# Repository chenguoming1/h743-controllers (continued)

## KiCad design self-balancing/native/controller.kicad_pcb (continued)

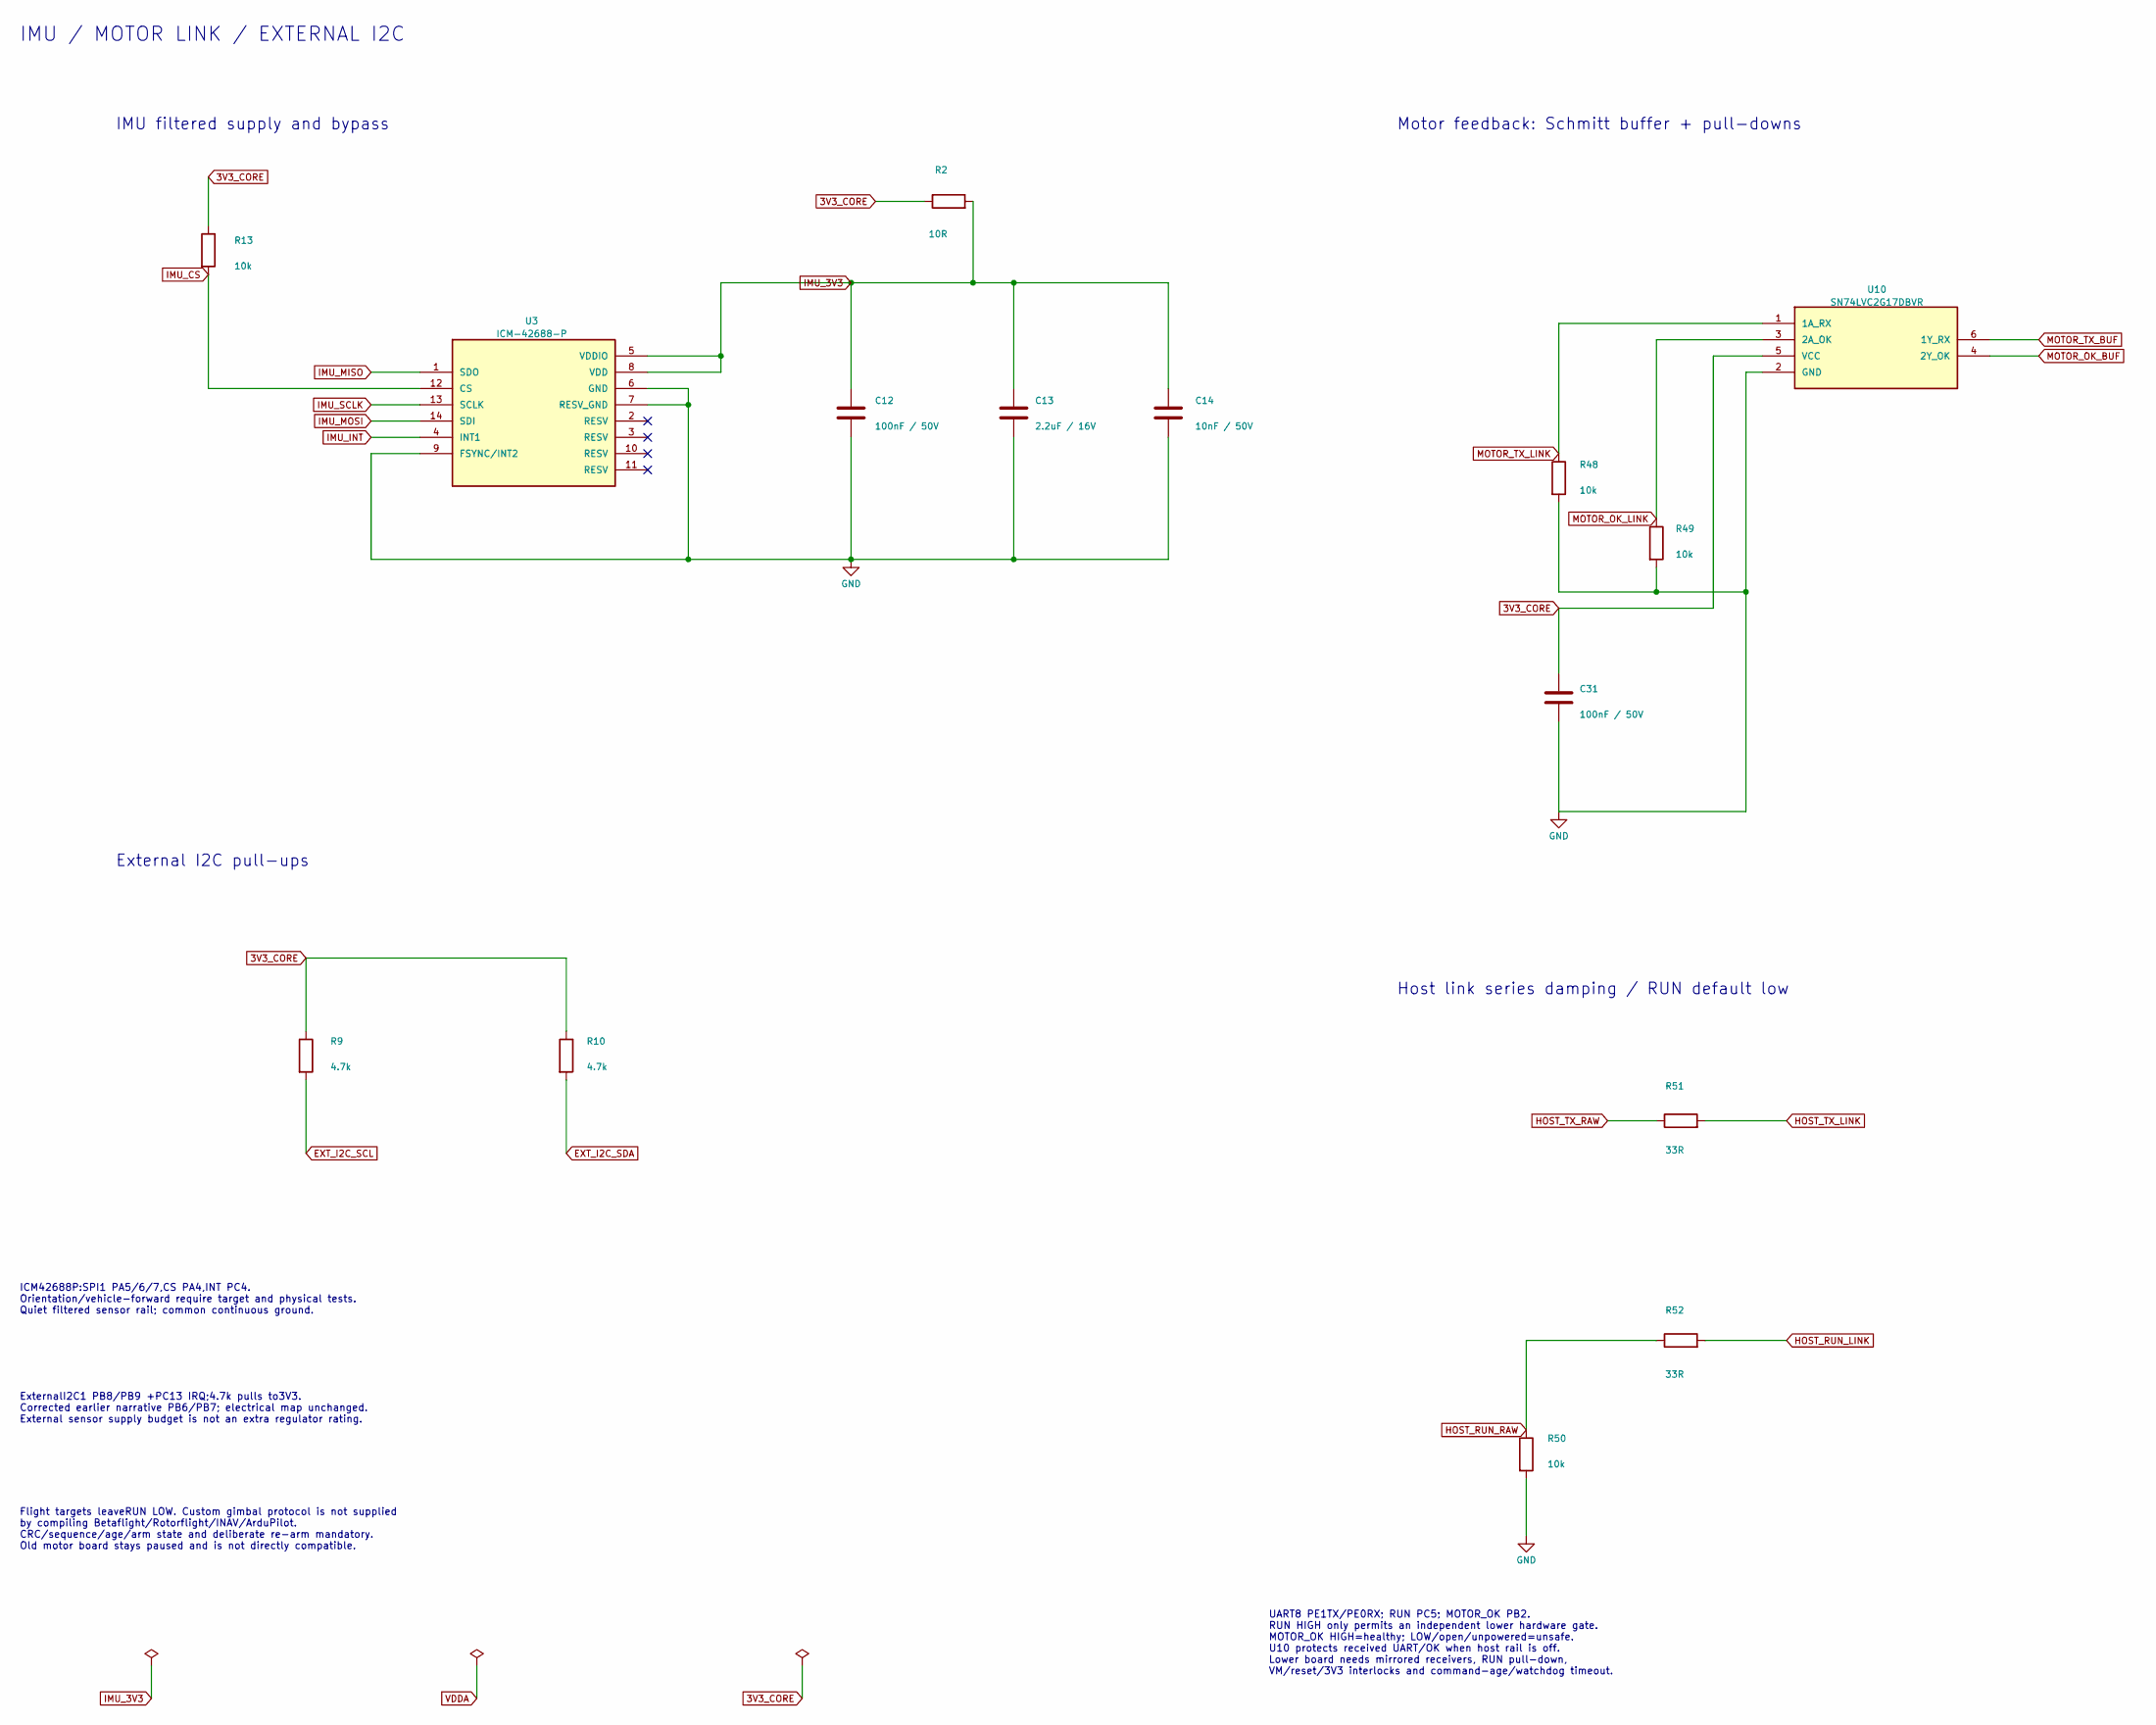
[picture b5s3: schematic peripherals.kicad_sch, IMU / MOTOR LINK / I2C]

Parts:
C12: 100nF / 50V; C12_C_0603_1608Metric; Manufacturer_Part_Number CC0603KRX7R9BB104; LCSC C14663
C13: 2.2uF / 16V; C13_C_0603_1608Metric; Manufacturer_Part_Number CL10A225KO8NNNC; LCSC C23630
C14: 10nF / 50V; C14_C_0603_1608Metric; Manufacturer_Part_Number 0603B103K500NT; LCSC C57112
C31: 100nF / 50V; C31_C_0603_1608Metric; Manufacturer_Part_Number CC0603KRX7R9BB104; LCSC C14663
R2: 10R; R2_R_0603_1608Metric; Manufacturer_Part_Number 0603WAF100JT5E; LCSC C22859
R9: 4.7k; R9_R_0603_1608Metric; Manufacturer_Part_Number 0603WAF4701T5E; LCSC C23162
R10: 4.7k; R10_R_0603_1608Metric; Manufacturer_Part_Number 0603WAF4701T5E; LCSC C23162
R13: 10k; R13_R_0603_1608Metric; Manufacturer_Part_Number 0603WAF1002T5E; LCSC C25804
R48: 10k; R48_R_0603_1608Metric; Manufacturer_Part_Number 0603WAF1002T5E; LCSC C25804
R49: 10k; R49_R_0603_1608Metric; Manufacturer_Part_Number 0603WAF1002T5E; LCSC C25804
R50: 10k; R50_R_0603_1608Metric; Manufacturer_Part_Number 0603WAF1002T5E; LCSC C25804
R51: 33R; R51_R_0603_1608Metric; Manufacturer_Part_Number 0603WAF330JT5E; LCSC C23140
R52: 33R; R52_R_0603_1608Metric; Manufacturer_Part_Number 0603WAF330JT5E; LCSC C23140
U3: ICM-42688-P; U3_LGA-14_3x2.5mm_P0.5mm_LayoutBorder3x4y; Manufacturer_Part_Number ICM-42688-P; LCSC C1850418
U10: SN74LVC2G17DBVR; U10_SOT-23-6; Manufacturer_Part_Number SN74LVC2G17DBVR; LCSC C10429

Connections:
EXT_I2C_SCL: R9.2; also elsewhere on the board
EXT_I2C_SDA: R10.2; also elsewhere on the board
GND: C12.2, C13.2, C14.2, C31.2, R48.2, R49.2, R50.2, U3.6 (GND), U3.7 (RESV_GND), U3.9 (FSYNC/INT2), U10.2 (GND); also elsewhere on the board
HOST_RUN_LINK: R52.2; also elsewhere on the board
HOST_RUN_RAW: R50.1, R52.1; also elsewhere on the board
HOST_TX_LINK: R51.2; also elsewhere on the board
HOST_TX_RAW: R51.1; also elsewhere on the board
IMU_3V3: C12.1, C13.1, C14.1, R2.2, U3.5 (VDDIO), U3.8 (VDD)
IMU_CS: R13.2, U3.12 (CS); also elsewhere on the board
IMU_INT: U3.4 (INT1); also elsewhere on the board
IMU_MISO: U3.1 (SDO); also elsewhere on the board
IMU_MOSI: U3.14 (SDI); also elsewhere on the board
IMU_SCLK: U3.13 (SCLK); also elsewhere on the board
MOTOR_OK_BUF: U10.4 (2Y_OK); also elsewhere on the board
MOTOR_OK_LINK: R49.1, U10.3 (2A_OK); also elsewhere on the board
MOTOR_TX_BUF: U10.6 (1Y_RX); also elsewhere on the board
MOTOR_TX_LINK: R48.1, U10.1 (1A_RX); also elsewhere on the board

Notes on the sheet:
IMU / MOTOR LINK / EXTERNAL I2C
IMU filtered supply and bypass
Motor feedback: Schmitt buffer + pull-downs
External I2C pull-ups
Host link series damping / RUN default low
ICM42688P:SPI1 PA5/6/7,CS PA4,INT PC4. Orientation/vehicle-forward require target and physical tests. Quiet filtered sensor rail; common continuous ground.
ExternalI2C1 PB8/PB9 +PC13 IRQ;4.7k pulls to3V3. Corrected earlier narrative PB6/PB7; electrical map unchanged. External sensor supply budget is not an extra regulator rating.
UART8 PE1TX/PE0RX; RUN PC5; MOTOR_OK PB2. RUN HIGH only permits an independent lower hardware gate. MOTOR_OK HIGH=healthy; LOW/open/unpowered=unsafe. U10 protects received UART/OK when host rail is off. Lower board needs mirrored receivers, RUN pull-down, VM/reset/3V3 interlocks and command-age/wat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
Flight targets leaveRUN LOW. Custom gimbal protocol is not supplied by compiling Betaflight/Rotorflight/INAV/ArduPilot. CRC/sequence/age/arm state and deliberate re-arm mandatory. Old motor board stays paused and is not directly compatible.

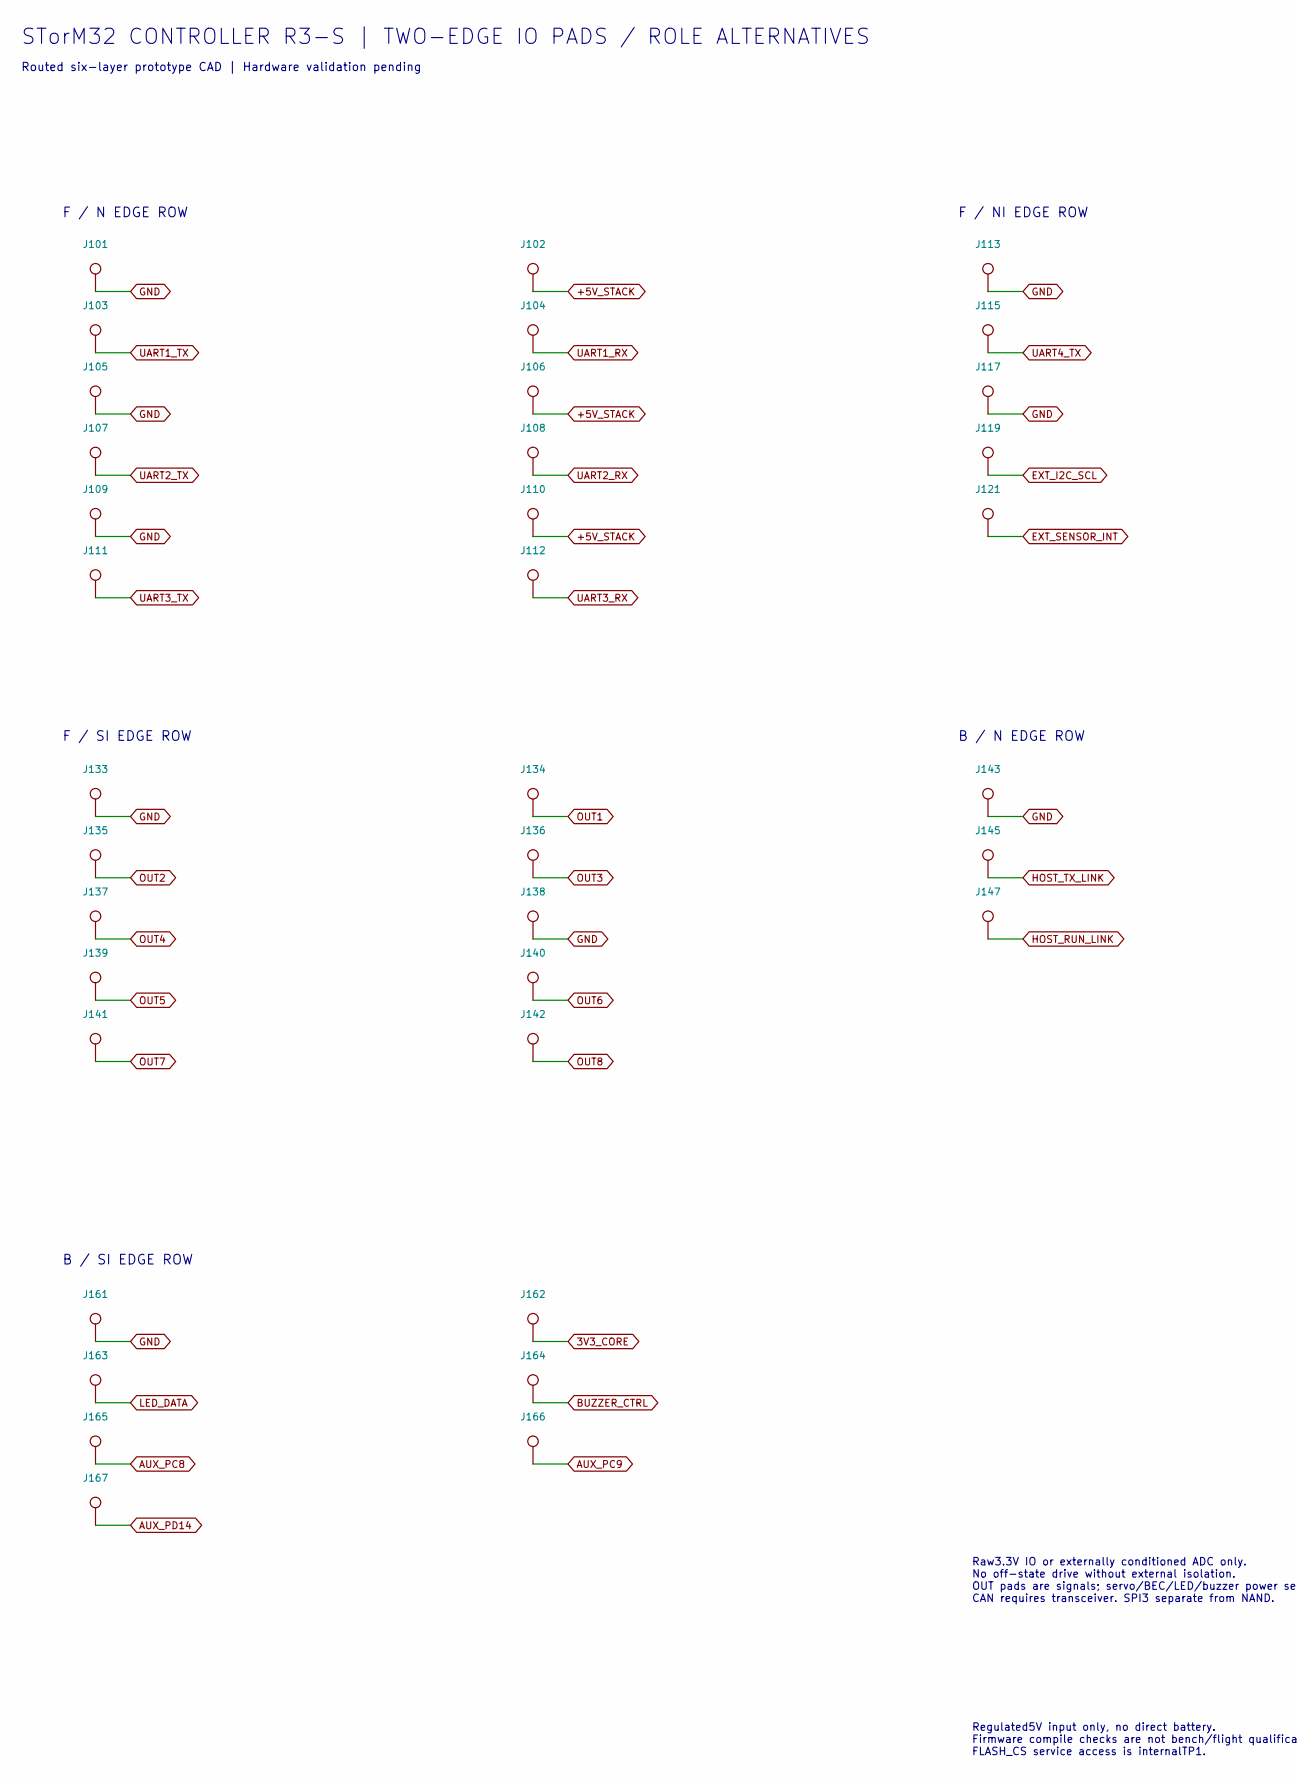
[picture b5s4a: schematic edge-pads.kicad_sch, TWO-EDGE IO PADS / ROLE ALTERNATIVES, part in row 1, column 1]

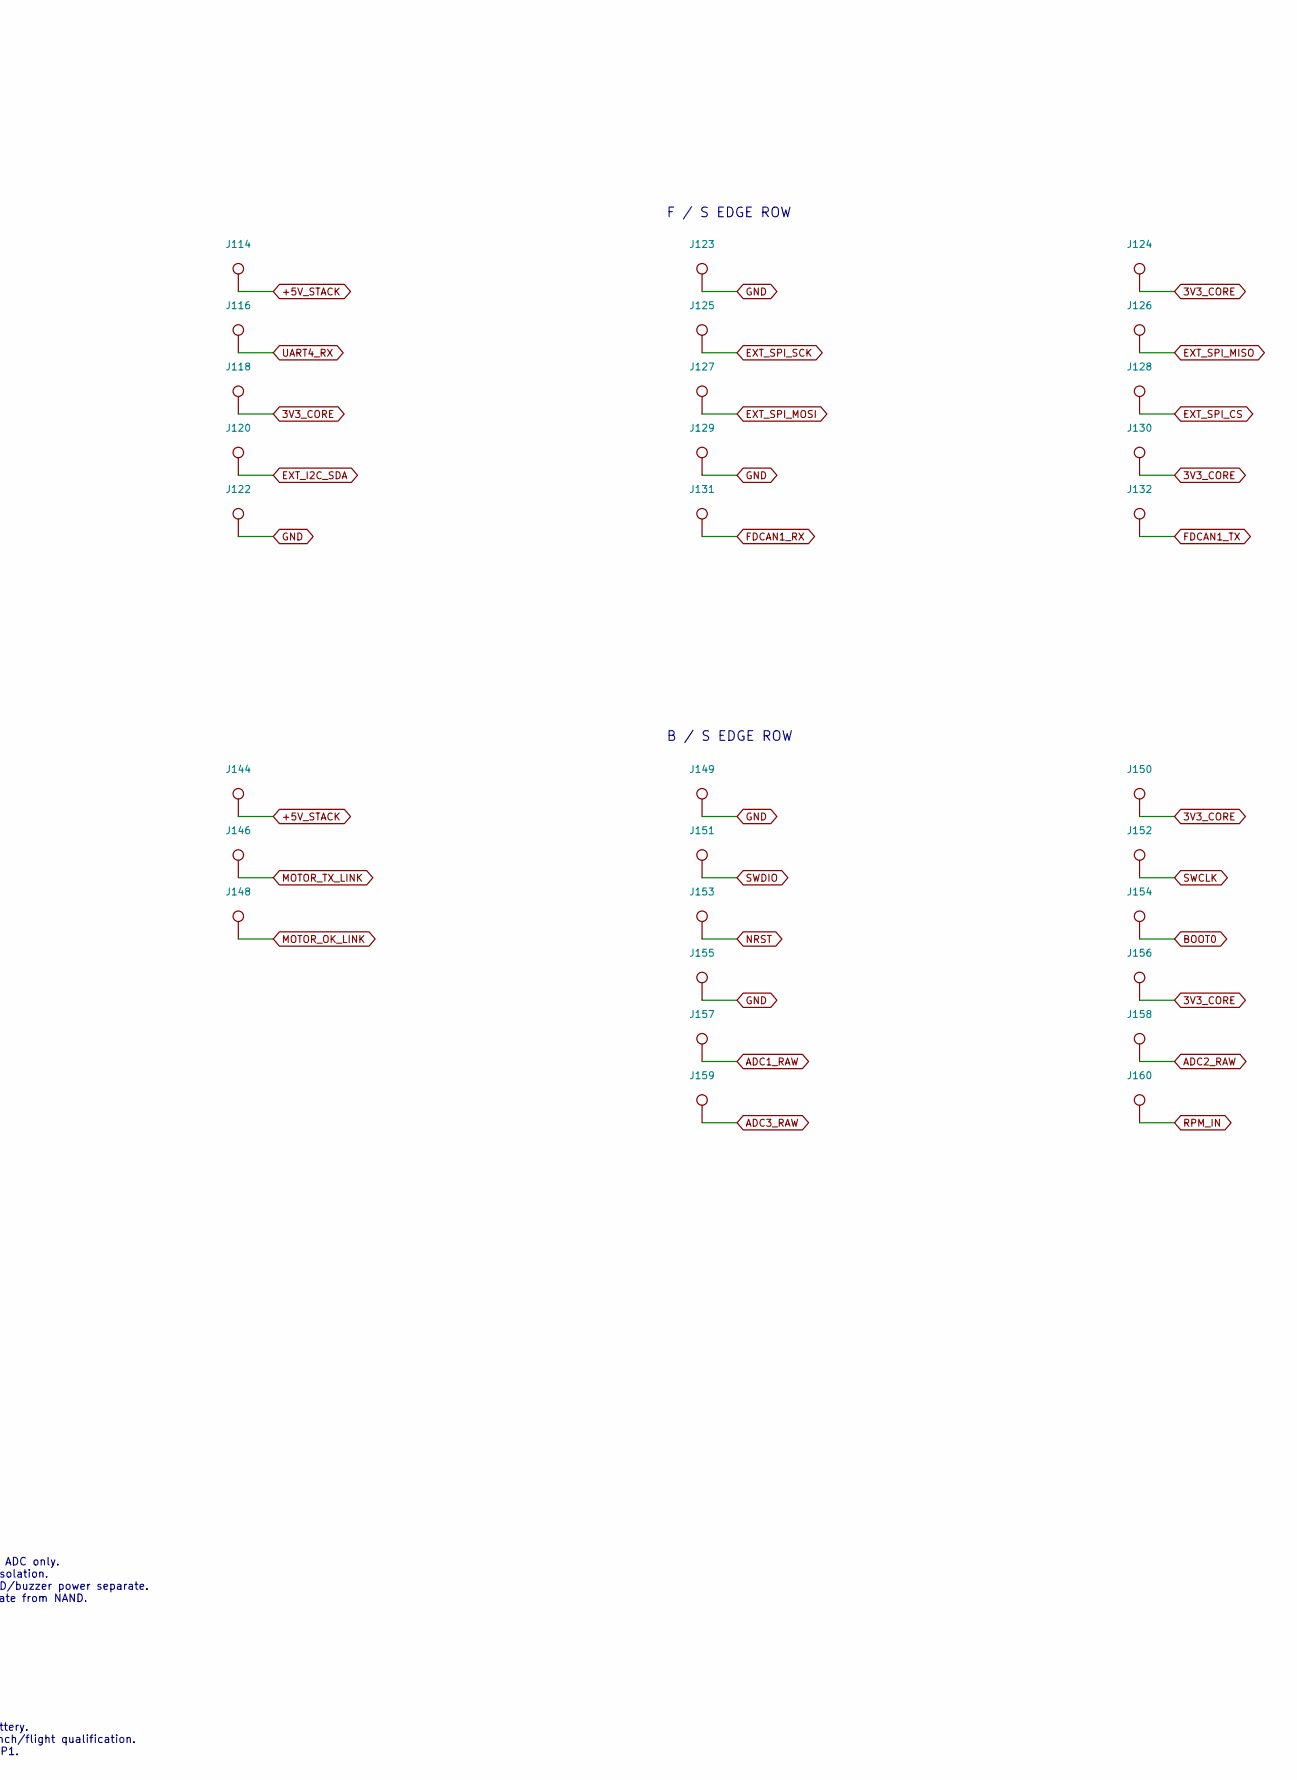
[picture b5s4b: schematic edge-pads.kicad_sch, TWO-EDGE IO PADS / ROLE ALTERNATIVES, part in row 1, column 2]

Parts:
J101, J105, J109, J113, J117, J122, J123, J129, J133, J138, J149, J155, J161: G; WirePad_1.6x2.0mm; Manufacturer_Part_Number PCB solder pad
J102, J106, J110, J114: 5V; WirePad_1.6x2.0mm; Manufacturer_Part_Number PCB solder pad
J103: T1; WirePad_1.6x2.0mm; Manufacturer_Part_Number PCB solder pad
J104: R1; WirePad_1.6x2.0mm; Manufacturer_Part_Number PCB solder pad
J107: T2; WirePad_1.6x2.0mm; Manufacturer_Part_Number PCB solder pad
J108: R2; WirePad_1.6x2.0mm; Manufacturer_Part_Number PCB solder pad
J111: T3; WirePad_1.6x2.0mm; Manufacturer_Part_Number PCB solder pad
J112: R3; WirePad_1.6x2.0mm; Manufacturer_Part_Number PCB solder pad
J115: T4; WirePad_1.6x2.0mm; Manufacturer_Part_Number PCB solder pad
J116: R4; WirePad_1.6x2.0mm; Manufacturer_Part_Number PCB solder pad
J118, J124, J130, J156, J162: 3V3; WirePad_1.6x2.0mm; Manufacturer_Part_Number PCB solder pad
J119: SCL; WirePad_1.6x2.0mm; Manufacturer_Part_Number PCB solder pad
J120: SDA; WirePad_1.6x2.0mm; Manufacturer_Part_Number PCB solder pad
J121: INT; WirePad_1.6x2.0mm; Manufacturer_Part_Number PCB solder pad
J125: SCK; WirePad_1.6x2.0mm; Manufacturer_Part_Number PCB solder pad
J126: MISO; WirePad_1.6x2.0mm; Manufacturer_Part_Number PCB solder pad
J127: MOSI; WirePad_1.6x2.0mm; Manufacturer_Part_Number PCB solder pad
J128: CS; WirePad_1.6x2.0mm; Manufacturer_Part_Number PCB solder pad
J131: CAN_RX; WirePad_1.6x2.0mm; Manufacturer_Part_Number PCB solder pad
J132: CAN_TX; WirePad_1.6x2.0mm; Manufacturer_Part_Number PCB solder pad
J134: OUT1; WirePad_1.6x2.0mm; Manufacturer_Part_Number PCB solder pad
J135: OUT2; WirePad_1.6x2.0mm; Manufacturer_Part_Number PCB solder pad
J136: OUT3; WirePad_1.6x2.0mm; Manufacturer_Part_Number PCB solder pad
J137: OUT4; WirePad_1.6x2.0mm; Manufacturer_Part_Number PCB solder pad
J139: OUT5; WirePad_1.6x2.0mm; Manufacturer_Part_Number PCB solder pad
J140: OUT6; WirePad_1.6x2.0mm; Manufacturer_Part_Number PCB solder pad
J141: OUT7; WirePad_1.6x2.0mm; Manufacturer_Part_Number PCB solder pad
J142: OUT8; WirePad_1.6x2.0mm; Manufacturer_Part_Number PCB solder pad
J143: G_LINK; WirePad_3.6x2.0mm; Manufacturer_Part_Number PCB solder pad
J144: 5V_LINK; WirePad_3.6x2.0mm; Manufacturer_Part_Number PCB solder pad
J145: LINK_TX; WirePad_1.6x2.0mm; Manufacturer_Part_Number PCB solder pad
J146: LINK_RX; WirePad_1.6x2.0mm; Manufacturer_Part_Number PCB solder pad
J147: RUN; WirePad_1.6x2.0mm; Manufacturer_Part_Number PCB solder pad
J148: M_OK; WirePad_1.6x2.0mm; Manufacturer_Part_Number PCB solder pad
J150: VTREF; WirePad_1.6x2.0mm; Manufacturer_Part_Number PCB solder pad
J151: SWDIO; WirePad_1.6x2.0mm; Manufacturer_Part_Number PCB solder pad
J152: SWCLK; WirePad_1.6x2.0mm; Manufacturer_Part_Number PCB solder pad
J153: NRST; WirePad_1.6x2.0mm; Manufacturer_Part_Number PCB solder pad
J154: BOOT; WirePad_1.6x2.0mm; Manufacturer_Part_Number PCB solder pad
J157: ADC1; WirePad_1.6x2.0mm; Manufacturer_Part_Number PCB solder pad
J158: ADC2; WirePad_1.6x2.0mm; Manufacturer_Part_Number PCB solder pad
J159: ADC3; WirePad_1.6x2.0mm; Manufacturer_Part_Number PCB solder pad
J160: RPM; WirePad_1.6x2.0mm; Manufacturer_Part_Number PCB solder pad
J163: LED; WirePad_1.6x2.0mm; Manufacturer_Part_Number PCB solder pad
J164: BUZ; WirePad_1.6x2.0mm; Manufacturer_Part_Number PCB solder pad
J165: PC8; WirePad_1.6x2.0mm; Manufacturer_Part_Number PCB solder pad
J166: PC9; WirePad_1.6x2.0mm; Manufacturer_Part_Number PCB solder pad
J167: PD14; WirePad_1.6x2.0mm; Manufacturer_Part_Number PCB solder pad

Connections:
+5V_STACK: J102.1, J106.1, J110.1, J114.1, J144.1; also elsewhere on the board
ADC1_RAW: J157.1; also elsewhere on the board
ADC2_RAW: J158.1; also elsewhere on the board
ADC3_RAW: J159.1; also elsewhere on the board
AUX_PC8: J165.1; also elsewhere on the board
AUX_PC9: J166.1; also elsewhere on the board
AUX_PD14: J167.1; also elsewhere on the board
BOOT0: J154.1; also elsewhere on the board
BUZZER_CTRL: J164.1; also elsewhere on the board
EXT_I2C_SCL: J119.1; also elsewhere on the board
EXT_I2C_SDA: J120.1; also elsewhere on the board
EXT_SENSOR_INT: J121.1; also elsewhere on the board
EXT_SPI_CS: J128.1; also elsewhere on the board
EXT_SPI_MISO: J126.1; also elsewhere on the board
EXT_SPI_MOSI: J127.1; also elsewhere on the board
EXT_SPI_SCK: J125.1; also elsewhere on the board
FDCAN1_RX: J131.1; also elsewhere on the board
FDCAN1_TX: J132.1; also elsewhere on the board
GND: J101.1, J105.1, J109.1, J113.1, J117.1, J122.1, J123.1, J129.1, J133.1, J138.1, J143.1, J149.1, J155.1, J161.1; also elsewhere on the board
HOST_RUN_LINK: J147.1; also elsewhere on the board
HOST_TX_LINK: J145.1; also elsewhere on the board
LED_DATA: J163.1; also elsewhere on the board
MOTOR_OK_LINK: J148.1; also elsewhere on the board
MOTOR_TX_LINK: J146.1; also elsewhere on the board
NRST: J153.1; also elsewhere on the board
OUT1: J134.1; also elsewhere on the board
OUT2: J135.1; also elsewhere on the board
OUT3: J136.1; also elsewhere on the board
OUT4: J137.1; also elsewhere on the board
OUT5: J139.1; also elsewhere on the board
OUT6: J140.1; also elsewhere on the board
OUT7: J141.1; also elsewhere on the board
OUT8: J142.1; also elsewhere on the board
RPM_IN: J160.1; also elsewhere on the board
SWCLK: J152.1; also elsewhere on the board
SWDIO: J151.1; also elsewhere on the board
UART1_RX: J104.1; also elsewhere on the board
UART1_TX: J103.1; also elsewhere on the board
UART2_RX: J108.1; also elsewhere on the board
UART2_TX: J107.1; also elsewhere on the board
UART3_RX: J112.1; also elsewhere on the board
UART3_TX: J111.1; also elsewhere on the board
UART4_RX: J116.1; also elsewhere on the board
UART4_TX: J115.1; also elsewhere on the board

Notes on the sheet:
STorM32 CONTROLLER R3-S | TWO-EDGE IO PADS / ROLE ALTERNATIVES
Routed six-layer prototype CAD | Hardware validation pending
F / N EDGE ROW
F / NI EDGE ROW
F / S EDGE ROW
F / SI EDGE ROW
B / N EDGE ROW
B / S EDGE ROW
B / SI EDGE ROW
Raw3.3V IO or externally conditioned ADC only. No off-state drive without external isolation. OUT pads are signals; servo/BEC/LED/buzzer power separate. CAN requires transceiver. SPI3 separate from NAND.
Regulated5V input only, no direct battery. Firmware compile checks are not bench/flight qualification. FLASH_CS service access is internalTP1.

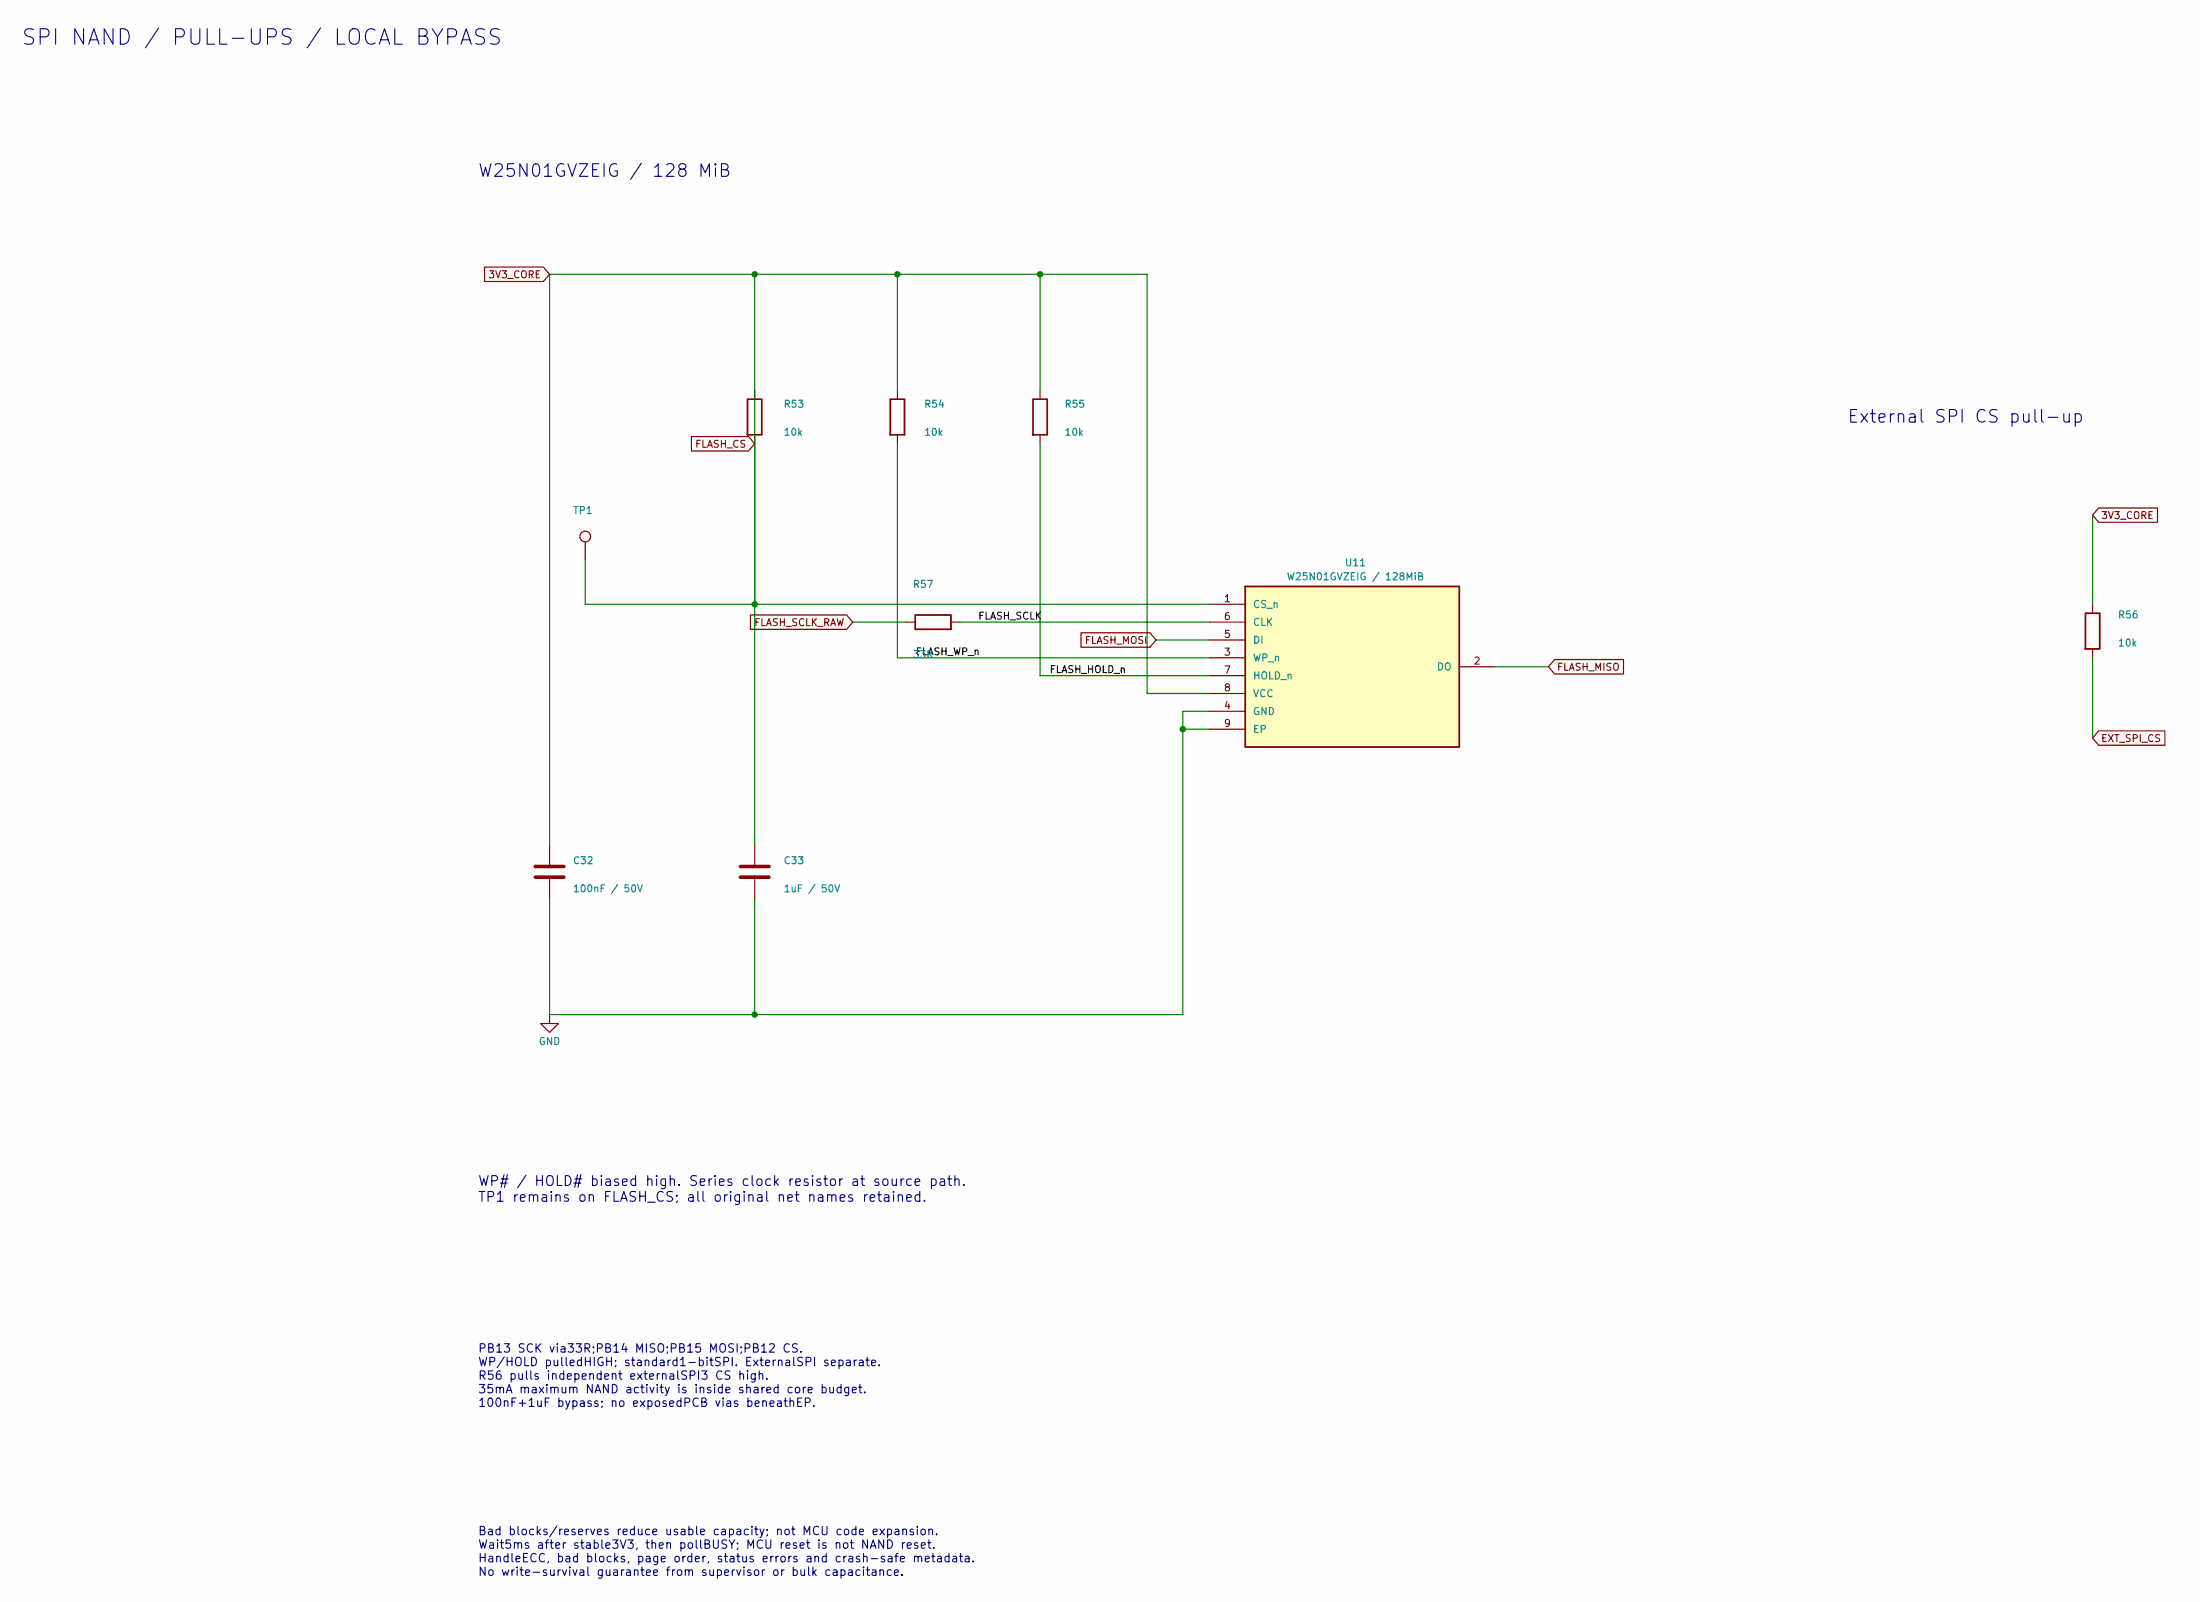
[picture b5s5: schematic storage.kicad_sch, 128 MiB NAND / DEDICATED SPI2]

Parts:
C32: 100nF / 50V; C32_C_0603_1608Metric; Manufacturer_Part_Number CC0603KRX7R9BB104; LCSC C14663
C33: 1uF / 50V; C33_C_0603_1608Metric; Manufacturer_Part_Number CL10A105KB8NNNC; LCSC C15849
R53: 10k; R53_R_0603_1608Metric; Manufacturer_Part_Number 0603WAF1002T5E; LCSC C25804
R54: 10k; R54_R_0603_1608Metric; Manufacturer_Part_Number 0603WAF1002T5E; LCSC C25804
R55: 10k; R55_R_0603_1608Metric; Manufacturer_Part_Number 0603WAF1002T5E; LCSC C25804
R56: 10k; R56_R_0603_1608Metric; Manufacturer_Part_Number 0603WAF1002T5E; LCSC C25804
R57: 33R; R57_R_0603_1608Metric; Manufacturer_Part_Number 0603WAF330JT5E; LCSC C23140
TP1: FLASH_CS service; TestPoint_Pad_D1.0mm_R3S_NoRing; Manufacturer_Part_Number PCB test point
U11: W25N01GVZEIG / 128MiB; U11_WSON-8-1EP_8x6mm_P1.27mm_EP3.4x4.3mm; Manufacturer_Part_Number W25N01GVZEIG; LCSC C88868

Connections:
/storage/FLASH_HOLD_n: R55.2, U11.7 (HOLD_n)
/storage/FLASH_SCLK: R57.2, U11.6 (CLK)
/storage/FLASH_WP_n: R54.2, U11.3 (WP_n)
EXT_SPI_CS: R56.2; also elsewhere on the board
FLASH_MISO: U11.2 (DO); also elsewhere on the board
FLASH_MOSI: U11.5 (DI); also elsewhere on the board
FLASH_SCLK_RAW: R57.1; also elsewhere on the board
GND: C32.2, C33.2, U11.4 (GND), U11.9 (EP); also elsewhere on the board

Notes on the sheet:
SPI NAND / PULL-UPS / LOCAL BYPASS
W25N01GVZEIG / 128 MiB
External SPI CS pull-up
WP# / HOLD# biased high. Series clock resistor at source path. TP1 remains on FLASH_CS; all original net names retained.
PB13 SCK via33R;PB14 MISO;PB15 MOSI;PB12 CS. WP/HOLD pulledHIGH; standard1-bitSPI. ExternalSPI separate. R56 pulls independent externalSPI3 CS high. 35mA maximum NAND activity is inside shared core budget. 100nF+1uF bypass; no exposedPCB vias beneathEP.
Bad blocks/reserves reduce usable capacity; not MCU code expansion. Wait5ms after stable3V3, then pollBUSY; MCU reset is not NAND reset. HandleECC, bad blocks, page order, status errors and crash-safe metadata. No write-survival guarantee from supervisor or bulk capacitance.

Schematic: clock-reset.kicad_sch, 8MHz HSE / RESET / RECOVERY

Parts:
C15: 100nF / 50V; C15_C_0603_1608Metric; Manufacturer_Part_Number CC0603KRX7R9BB104; LCSC C14663
C34: 18pF C0G / tune; C34_C_0603_1608Metric; Manufacturer_Part_Number CL10C180JB8NNNC; LCSC C1647
C35: 18pF C0G / tune; C35_C_0603_1608Metric; Manufacturer_Part_Number CL10C180JB8NNNC; LCSC C1647
C38: 100nF / 50V; C38_C_0603_1608Metric; Manufacturer_Part_Number CC0603KRX7R9BB104; LCSC C14663
R3: 10k; R3_R_0603_1608Metric; Manufacturer_Part_Number 0603WAF1002T5E; LCSC C25804
R4: 10k; R4_R_0603_1608Metric; Manufacturer_Part_Number 0603WAF1002T5E; LCSC C25804
R58: 0R / HSE tune; R58_R_0603_1608Metric; Manufacturer_Part_Number 0603WAF0000T5E; LCSC C21189
U12: TLV803EA29DBZR; U12_SOT-23; Manufacturer_Part_Number TLV803EA29DBZR; LCSC C1852114
X1: 8MHz / CL12pF; TXC_A308000003_3225_2pad; Manufacturer_Part_Number A308000003; LCSC C409345

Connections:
/clock/HSE_XOUT: C35.1, R58.2, X1.2
BOOT0: R3.1; also elsewhere on the board
GND: C15.2, C34.2, C35.2, C38.2, R3.2, U12.1 (GND); also elsewhere on the board
HSE_IN: C34.1, X1.1; also elsewhere on the board
HSE_OUT: R58.1; also elsewhere on the board
NRST: C15.1, R4.2, U12.2 (RESET); also elsewhere on the board

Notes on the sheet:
CLOCK / RESET / BOOT
8 MHz crystal network
2.9 V reset supervisor + pull-up / filter
BOOT0 default low
Crystal load capacitors: tune from oscillator validation Preserved values: 18 pF C0G, 0 ohm series tuning link
PH0pin12/PH1pin13; TXC A308000003:8MHz,CL12pF. 2x18pF assumes3pF effective stray; tune on hardware. ESR300Ohm,C0<=3pF preliminary gmcrit0.682mA/V. R58 drive-tuning position. Exact-lot/startup/drive checks remain.
EA29~2.93V open-drain reset,200ms release. NRST shared withSWD/reset pad;BOOT0 defaults10kLOW. EA29 avoids EA30 release-margin overlap with buck tolerance. Interrupted NAND writes can still fail. Test brownout ramps.
InternalLDO mode; correctVOS/flash wait states/clocks. HSE_VALUE=8000000. 480MHz requires compatible silicon/temperature. BOOT_ADD0/1 recovery. SWD primary; verifyUSBDFU and cold power cycle. RUN PC5/source-disable PE12 selected away from ROM output drive.

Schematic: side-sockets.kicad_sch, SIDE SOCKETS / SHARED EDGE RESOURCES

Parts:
J3: MOTOR / 6-wire; LianXin_XDWF-0910_06P_Horizontal; Manufacturer_Part_Number XDWF-0910-06P; LCSC C7527621
J4: EXT SPI SENSOR; J4_JST_SH_SM08B-SRSS-TB_1x08-1MP_P1.00mm_Horizontal; Manufacturer_Part_Number SM08B-SRSS-TB(LF)(SN); LCSC C160407
J5: GPS / UART4; J5_JST_SH_SM04B-SRSS-TB_1x04-1MP_P1.00mm_Horizontal; Manufacturer_Part_Number SM04B-SRSS-TB(LF)(SN); LCSC C160404

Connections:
+5V_STACK: J3.1, J5.1; also elsewhere on the board
EXT_SENSOR_INT: J4.7; also elsewhere on the board
EXT_SPI_CS: J4.6; also elsewhere on the board
EXT_SPI_MISO: J4.5; also elsewhere on the board
EXT_SPI_MOSI: J4.4; also elsewhere on the board
EXT_SPI_SCK: J4.3; also elsewhere on the board
GND: J3.2, J3.MP (ANCHORS), J4.2, J4.8, J4.MP (ANCHORS), J5.2, J5.MP (ANCHORS); also elsewhere on the board
HOST_RUN_LINK: J3.5; also elsewhere on the board
HOST_TX_LINK: J3.3; also elsewhere on the board
MOTOR_OK_LINK: J3.6; also elsewhere on the board
MOTOR_TX_LINK: J3.4; also elsewhere on the board
UART4_RX: J5.4; also elsewhere on the board
UART4_TX: J5.3; also elsewhere on the board

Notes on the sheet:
STorM32 CONTROLLER R3-S | SIDE SOCKETS / SHARED EDGE RESOURCES
Routed six-layer prototype CAD | Hardware validation pending
J3 MOTOR:Lian Xin6, rearwest; custom pinout
1 5V_STACK input /2GND /3hostTX /4motorTX /5RUN /6MOTOR_OK. Duplicates existing link after damping and before receive buffer. Use socket OR pads for one endpoint. Anchors are not extra cable returns. Motor board needs protected inputs and default-off independent gate. J3 carries total controller+GP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
J4 EXTERNALSPI SENSOR:JST8, rearwest
1 3V3 /2GND /3SCK /4MOSI /5MISO /6CS /7IRQ /8GND. DuplicatesSPI3 andPC13 IRQ pads. Not an independent sensor bus. One selectedCS/IRQ owner; do not parallel push-pull outputs. Short cable,3.3V, no off-state drive. No qualified spare power allowance. External sensor driver/clock/damping require targe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
J5 GPS UART4:JST4, reareast
1 5V_STACK output /2GND /3controllerTX /4controllerRX. TX goes to moduleRX and viceversa; signals3.3V. No5V onUSB-only power; do not connect a competing supply. CompassI2C andPPS are not carried by this socket. Verify module cable pinout; no universalGPS plug compatibility.
Friction retention; correct crimps and independent strain relief. J3 usesZYA1001H mate; mated envelope/cross-mating unqualified. J4/J5 plainSHR-08V-S/SHR-04V-S; use rated wire/contact combination. 2.9mm headers;JST mated2.95mm. Plan4mm rear airgap plus opposite parts. USBovermold/harness/stack chec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

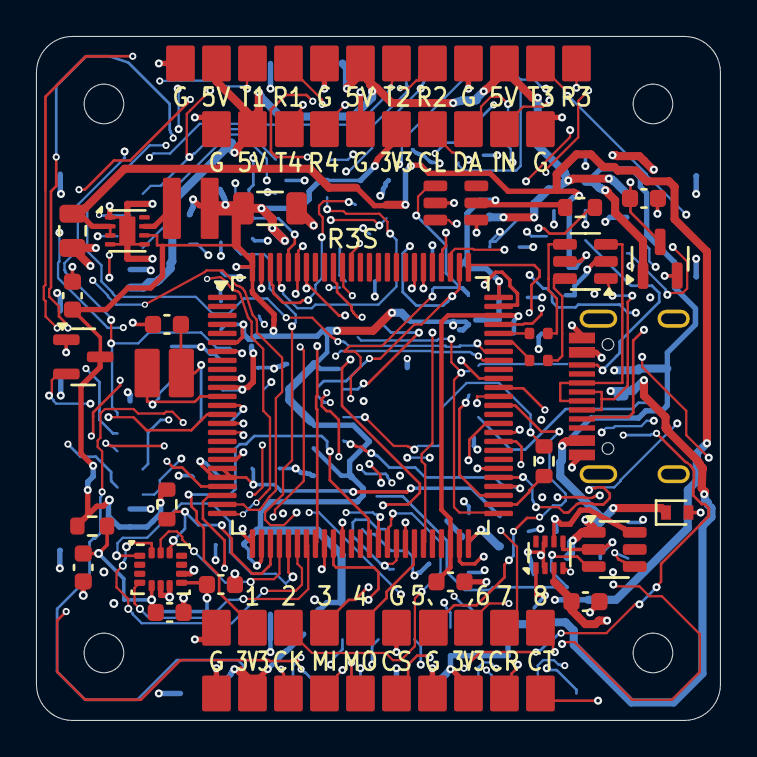
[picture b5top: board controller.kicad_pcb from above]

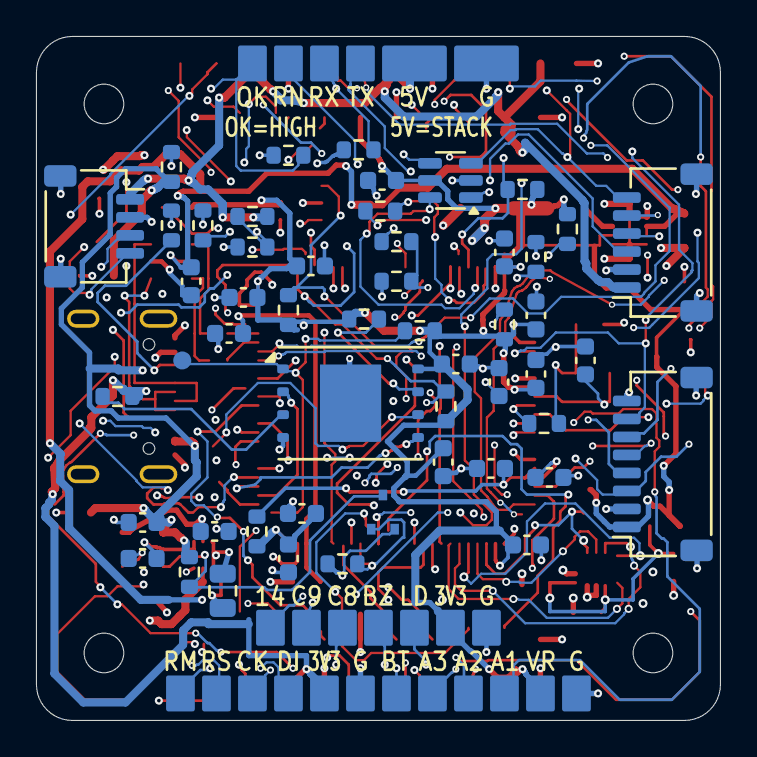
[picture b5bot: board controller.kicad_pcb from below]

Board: 6 copper layers, 38.0 x 38.0 mm, 151 parts (76 on the bottom side), 85 nets.

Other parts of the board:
H1, H2, H3, H4: MountingHole_2.2mm_M2
